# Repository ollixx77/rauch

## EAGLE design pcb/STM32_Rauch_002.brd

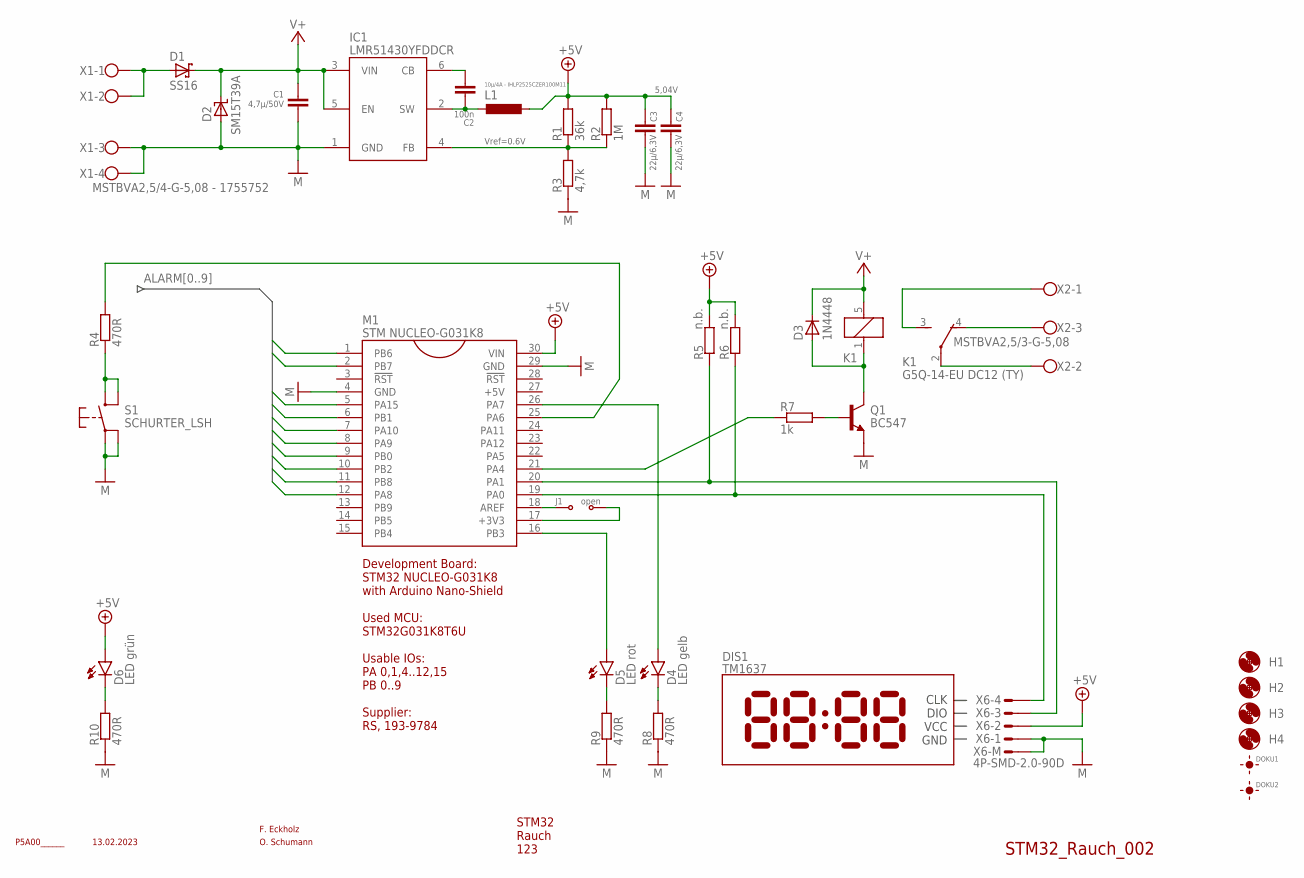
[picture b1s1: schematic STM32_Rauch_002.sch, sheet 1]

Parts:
C1: 4,7µ/50V; CAPC1210
C2: 100n; CAPC0603
C3, C4: 22µ/6,3V; CAPC1206
D1: SS16; DIOM-SMA
D2: SM15T39A; DIOM-SMC
D3: 1N4448; SOD323
D4: LED gelb; LEDC1608
D5: LED rot; LEDC1608
D6: LED grün; LEDC1608
DIS1: TM1637
DOKU1, DOKU2: PAD-FIDU-R200; FIDU_RUND-2MM
DOKU4: STM32_Rauch_002; DOKU-50-TOP
H1, H2, H3, H4: MOUNT-HOLE-3.2; MOUNT-HOLE-3,2
IC1: LMR51430YFDDCR; SOT23-6
J1: open; CON-SOLDERJUMPER
K1: G5Q-14-EU DC12 (TY); OMRON-G5Q
L1: 10µ/4A - IHLP2525CZER100M11; INDM0707
M1: STM NUCLEO-G031K8; NUCLEO32
Q1: BC547; SOT23
R1: 36k; RESC0603
R2: 1M; RESC0603
R3: 4,7k; RESC0603
R4, R8, R9, R10: 470R; RESC0603
R5, R6: n.b.; RESC0603
R7: 1k; RESC0603
S1: SCHURTER_LSH; SHURTER_LSH
X1: MSTBVA2,5/4-G-5,08 - 1755752; MSTBVA2,5/4-G-5,08
X2: MSTBVA2,5/3-G-5,08
X6: 4P-SMD-2.0-90D

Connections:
!RESET: M1.25 (PA6), R4.2
+5V: C3.2, C4.2, D6.2 (A), L1.2, M1.30 (VIN), R1.2, R2.2, R5.2, R6.2, X6.2; also elsewhere on the board
ALARM0: M1.1 (PB6); also elsewhere on the board
ALARM1: M1.2 (PB7); also elsewhere on the board
ALARM2: M1.5 (PA15); also elsewhere on the board
ALARM3: M1.6 (PB1); also elsewhere on the board
ALARM4: M1.7 (PA10); also elsewhere on the board
ALARM5: M1.8 (PA9); also elsewhere on the board
ALARM6: M1.9 (PB0); also elsewhere on the board
ALARM7: M1.10 (PB2); also elsewhere on the board
ALARM8: M1.11 (PB8); also elsewhere on the board
ALARM9: M1.12 (PA8); also elsewhere on the board
M: C1.1, C3.1, C4.1, D2.2 (A), IC1.1 (GND), M1.4 (GND), M1.29 (GND), Q1.2 (E), R3.1, R8.1, R9.1, R10.1, S1.1, S1.2, X1.3, X1.4, X6.1, X6.SS1, X6.SS2; also elsewhere on the board
unnamed: D3.A, K1.1 (COIL1), Q1.3 (C)
unnamed: D1.2 (A), X1.1, X1.2
unnamed: R4.1, S1.3 (S), S1.4 (S)
unnamed: D4.1 (C), R8.2
unnamed: Q1.1 (B), R7.2
unnamed: D5.1 (C), R9.2
unnamed: M1.21 (PA4), R7.1
unnamed: C2.1, IC1.6 (CB)
unnamed: C2.2, IC1.2 (SW), L1.1
unnamed: IC1.4 (FB), R1.1, R2.1, R3.2
unnamed: K1.2 (C), X2.2
unnamed: K1.3 (NO), X2.1
unnamed: K1.4 (NC), X2.3
unnamed: M1.19 (PA0), R6.1, X6.4
unnamed: D6.1 (C), R10.2
unnamed: J1.1, M1.18 (AREF)
unnamed: M1.20 (PA1), R5.1, X6.3
unnamed: D4.2 (A), M1.26 (PA7)
unnamed: D5.2 (A), M1.16 (PB3)
unnamed: J1.2, M1.17 (+3V3)
V+: C1.2, D1.1 (K), D2.1 (C), D3.C, IC1.3 (VIN), IC1.5 (EN), K1.5 (COIL2); also elsewhere on the board

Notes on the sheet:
O. Schumann
F. Eckholz
STM32 Rauch 123
P5A00______
13.02.2023
5,04V
Vref=0.6V
Development Board: STM32 NUCLEO-G031K8 with Arduino Nano-Shield Used MCU: STM32G031K8T6U Usable IOs: PA 0,1,4..12,15 PB 0..9 Supplier: RS, 193-9784

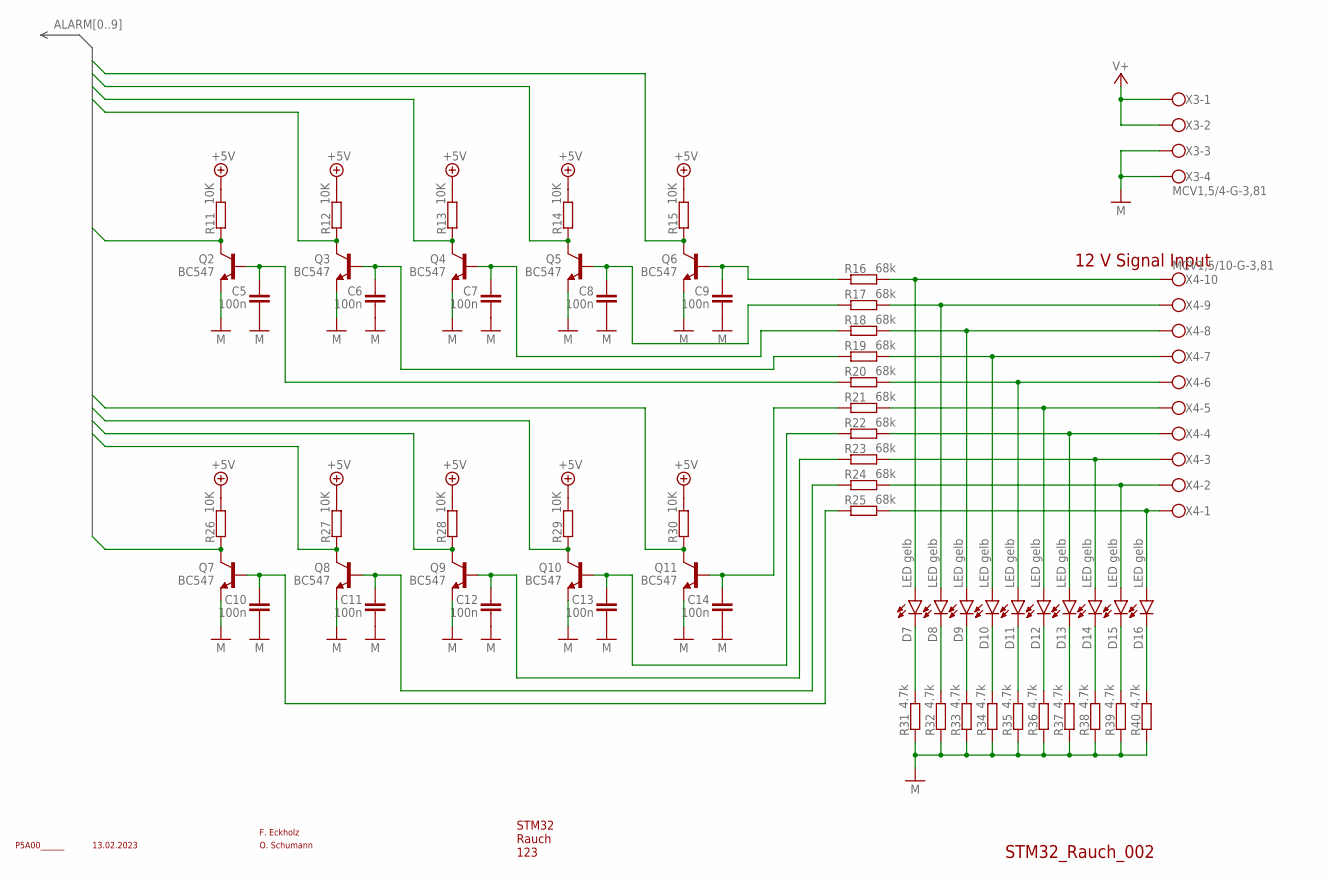
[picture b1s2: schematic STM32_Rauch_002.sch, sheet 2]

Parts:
C5, C6, C7, C8, C9, C10, C11, C12, C13, C14: 100n; CAPC0603
D7, D8, D9, D10, D11, D12, D13, D14, D15, D16: LED gelb; LEDC1608
DOKU4: STM32_Rauch_002; DOKU-50-TOP
Q2, Q3, Q4, Q5, Q6, Q7, Q8, Q9, Q10, Q11: BC547; SOT23
R11, R12, R13, R14, R15, R26, R27, R28, R29, R30: 10K; RESC0603
R16, R17, R18, R19, R20, R21, R22, R23, R24, R25: 68k; RESC0603
R31, R32, R33, R34, R35, R36, R37, R38, R39, R40: 4.7k; RESC0603
X3: MCV1,5/4-G-3,81
X4: MCV1,5/10-G-3,81

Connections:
+5V: R11.2, R12.2, R13.2, R14.2, R15.2, R26.2, R27.2, R28.2, R29.2, R30.2; also elsewhere on the board
ALARM0: Q6.3 (C), R15.1; also elsewhere on the board
ALARM1: Q5.3 (C), R14.1; also elsewhere on the board
ALARM2: Q4.3 (C), R13.1; also elsewhere on the board
ALARM3: Q3.3 (C), R12.1; also elsewhere on the board
ALARM4: Q2.3 (C), R11.1; also elsewhere on the board
ALARM5: Q11.3 (C), R30.1; also elsewhere on the board
ALARM6: Q10.3 (C), R29.1; also elsewhere on the board
ALARM7: Q9.3 (C), R28.1; also elsewhere on the board
ALARM8: Q8.3 (C), R27.1; also elsewhere on the board
ALARM9: Q7.3 (C), R26.1; also elsewhere on the board
M: C5.1, C6.1, C7.1, C8.1, C9.1, C10.1, C11.1, C12.1, C13.1, C14.1, Q2.2 (E), Q3.2 (E), Q4.2 (E), Q5.2 (E), Q6.2 (E), Q7.2 (E), Q8.2 (E), Q9.2 (E), Q10.2 (E), Q11.2 (E), R31.1, R32.1, R33.1, R34.1, R35.1, R36.1, R37.1, R38.1, R39.1, R40.1, X3.P$3, X3.P$4; also elsewhere on the board
unnamed: D7.2 (A), R16.2, X4.P$10
unnamed: D7.1 (C), R31.2
unnamed: C14.2, Q11.1 (B), R21.1
unnamed: D14.2 (A), R23.2, X4.P$3
unnamed: C13.2, Q10.1 (B), R22.1
unnamed: D8.2 (A), R17.2, X4.P$9
unnamed: D9.2 (A), R18.2, X4.P$8
unnamed: D10.2 (A), R19.2, X4.P$7
unnamed: D11.2 (A), R20.2, X4.P$6
unnamed: D12.2 (A), R21.2, X4.P$5
unnamed: D13.2 (A), R22.2, X4.P$4
unnamed: D15.2 (A), R24.2, X4.P$2
unnamed: D16.2 (A), R25.2, X4.P$1
unnamed: D8.1 (C), R32.2
unnamed: D9.1 (C), R33.2
unnamed: D10.1 (C), R34.2
unnamed: D11.1 (C), R35.2
unnamed: D12.1 (C), R36.2
unnamed: D13.1 (C), R37.2
unnamed: C12.2, Q9.1 (B), R23.1
unnamed: D14.1 (C), R38.2
unnamed: D15.1 (C), R39.2
unnamed: C11.2, Q8.1 (B), R24.1
unnamed: D16.1 (C), R40.2
unnamed: C9.2, Q6.1 (B), R16.1
unnamed: C8.2, Q5.1 (B), R17.1
unnamed: C7.2, Q4.1 (B), R18.1
unnamed: C6.2, Q3.1 (B), R19.1
unnamed: C10.2, Q7.1 (B), R25.1
unnamed: C5.2, Q2.1 (B), R20.1
V+: X3.P$1, X3.P$2; also elsewhere on the board

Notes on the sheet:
O. Schumann
F. Eckholz
STM32 Rauch 123
P5A00______
13.02.2023
12 V Signal Input

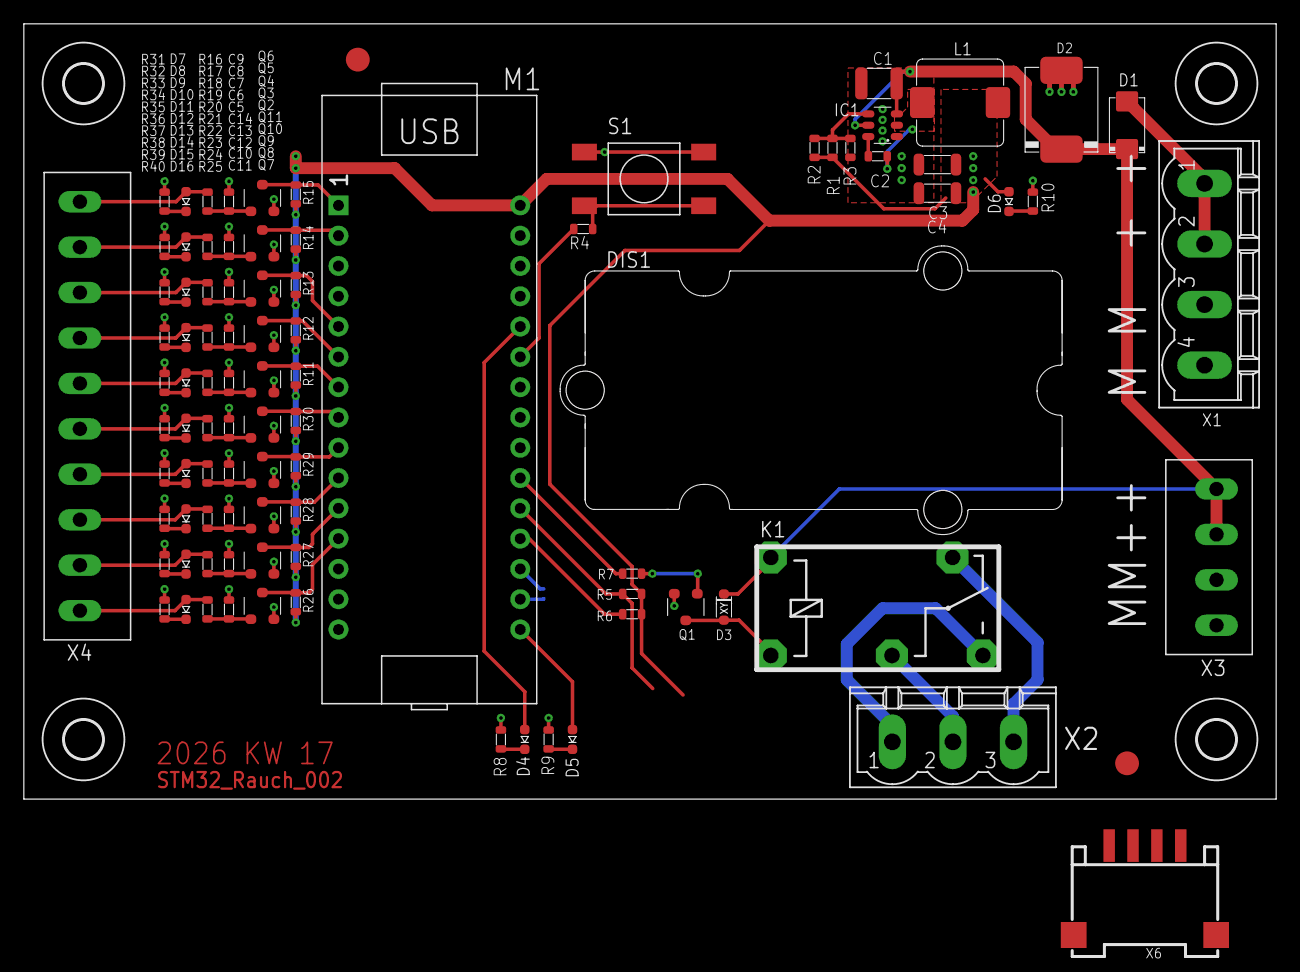
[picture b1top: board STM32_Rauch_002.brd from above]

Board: 2 copper layers, 105.0 x 65.0 mm, 100 parts (1 on the bottom side), 64 nets.

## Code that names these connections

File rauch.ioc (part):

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Mcu.Name=STM32G031K(4-6-8)Tx
Mcu.Package=LQFP32
Mcu.UserName=STM32G031K8Tx
PA0.Signal=GPIO_Output
PA1.Signal=GPIO_Output
PA10.Signal=GPIO_Input
PA13.GPIOParameters=GPIO_Label
PA13.GPIO_Label=T_JTMS
PA13.Mode=Serial_Wire
PA13.Signal=SYS_SWDIO
PA14-BOOT0.GPIOParameters=GPIO_Label
PA14-BOOT0.GPIO_Label=T_JTCK
PA14-BOOT0.Mode=Serial_Wire
PA14-BOOT0.Signal=SYS_SWCLK
PA15.Signal=GPIO_Input
PA2.GPIOParameters=GPIO_PuPd,GPIO_Label
PA2.GPIO_Label=T_VCP_TX
PA2.GPIO_PuPd=GPIO_PULLUP
PA2.Mode=Asynchronous
PA2.Signal=USART2_TX
PA3.GPIOParameters=GPIO_PuPd,GPIO_Label
PA3.GPIO_Label=T_VCP_RX
PA3.GPIO_PuPd=GPIO_PULLUP
PA3.Mode=Asynchronous
PA3.Signal=USART2_RX
PA4.Signal=GPIO_Output
PA6.GPIOParameters=GPIO_PuPd
PA6.GPIO_PuPd=GPIO_PULLUP
PA6.Signal=GPIO_Input
PA7.Signal=GPIO_Output
PA8.Signal=GPIO_Input
PA9.Signal=GPIO_Input
PB0.Signal=GPIO_Input
PB1.Signal=GPIO_Input
PB2.Signal=GPIO_Input
PB3.Signal=GPIO_Output
PB6.Signal=GPIO_Input
PB7.Signal=GPIO_Input
PB8.Signal=GPIO_Input
PC14-OSC32_IN\ (PC14).Mode=LSE-External-Oscillator
PC14-OSC32_IN\ (PC14).Signal=RCC_OSC32_IN
PC15-OSC32_OUT\ (PC15).Mode=LSE-External-Oscillator
PC15-OSC32_OUT\ (PC15).Signal=RCC_OSC32_OUT
PC6.GPIOParameters=GPIO_Label
PC6.GPIO_Label=LD3 [Green]
PC6.Signal=GPIO_Output
PF2\ -\ NRST.GPIOParameters=GPIO_Label
PF2\ -\ NRST.GPIO_Label=T_NRST
PF2\ -\ NRST.Signal=GPXTI2
RCC.HSE_VALUE=8000000
RCC.SYSCLKFreq_VALUE=16000000
board=NUCLEO-G031K8
boardIOC=true

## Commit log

2026-04-24 Update .gitignore for STM32 and debug files
    Added entries for STM32 development and various debug and output files to .gitignore.
2026-04-24 Init
2026-04-24 Refactor .gitignore for clarity and organization
    Updated .gitignore to include new patterns and remove unnecessary entries.
2026-04-24 Doku & PCB files
2026-04-25 corrected tm1637 7-segment mapping for chars ^_[]
2026-04-27 changed text

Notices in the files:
parts and their libraries:
frames: Copyright (C) Siemens AG, 2022 --RESTRICTED--
